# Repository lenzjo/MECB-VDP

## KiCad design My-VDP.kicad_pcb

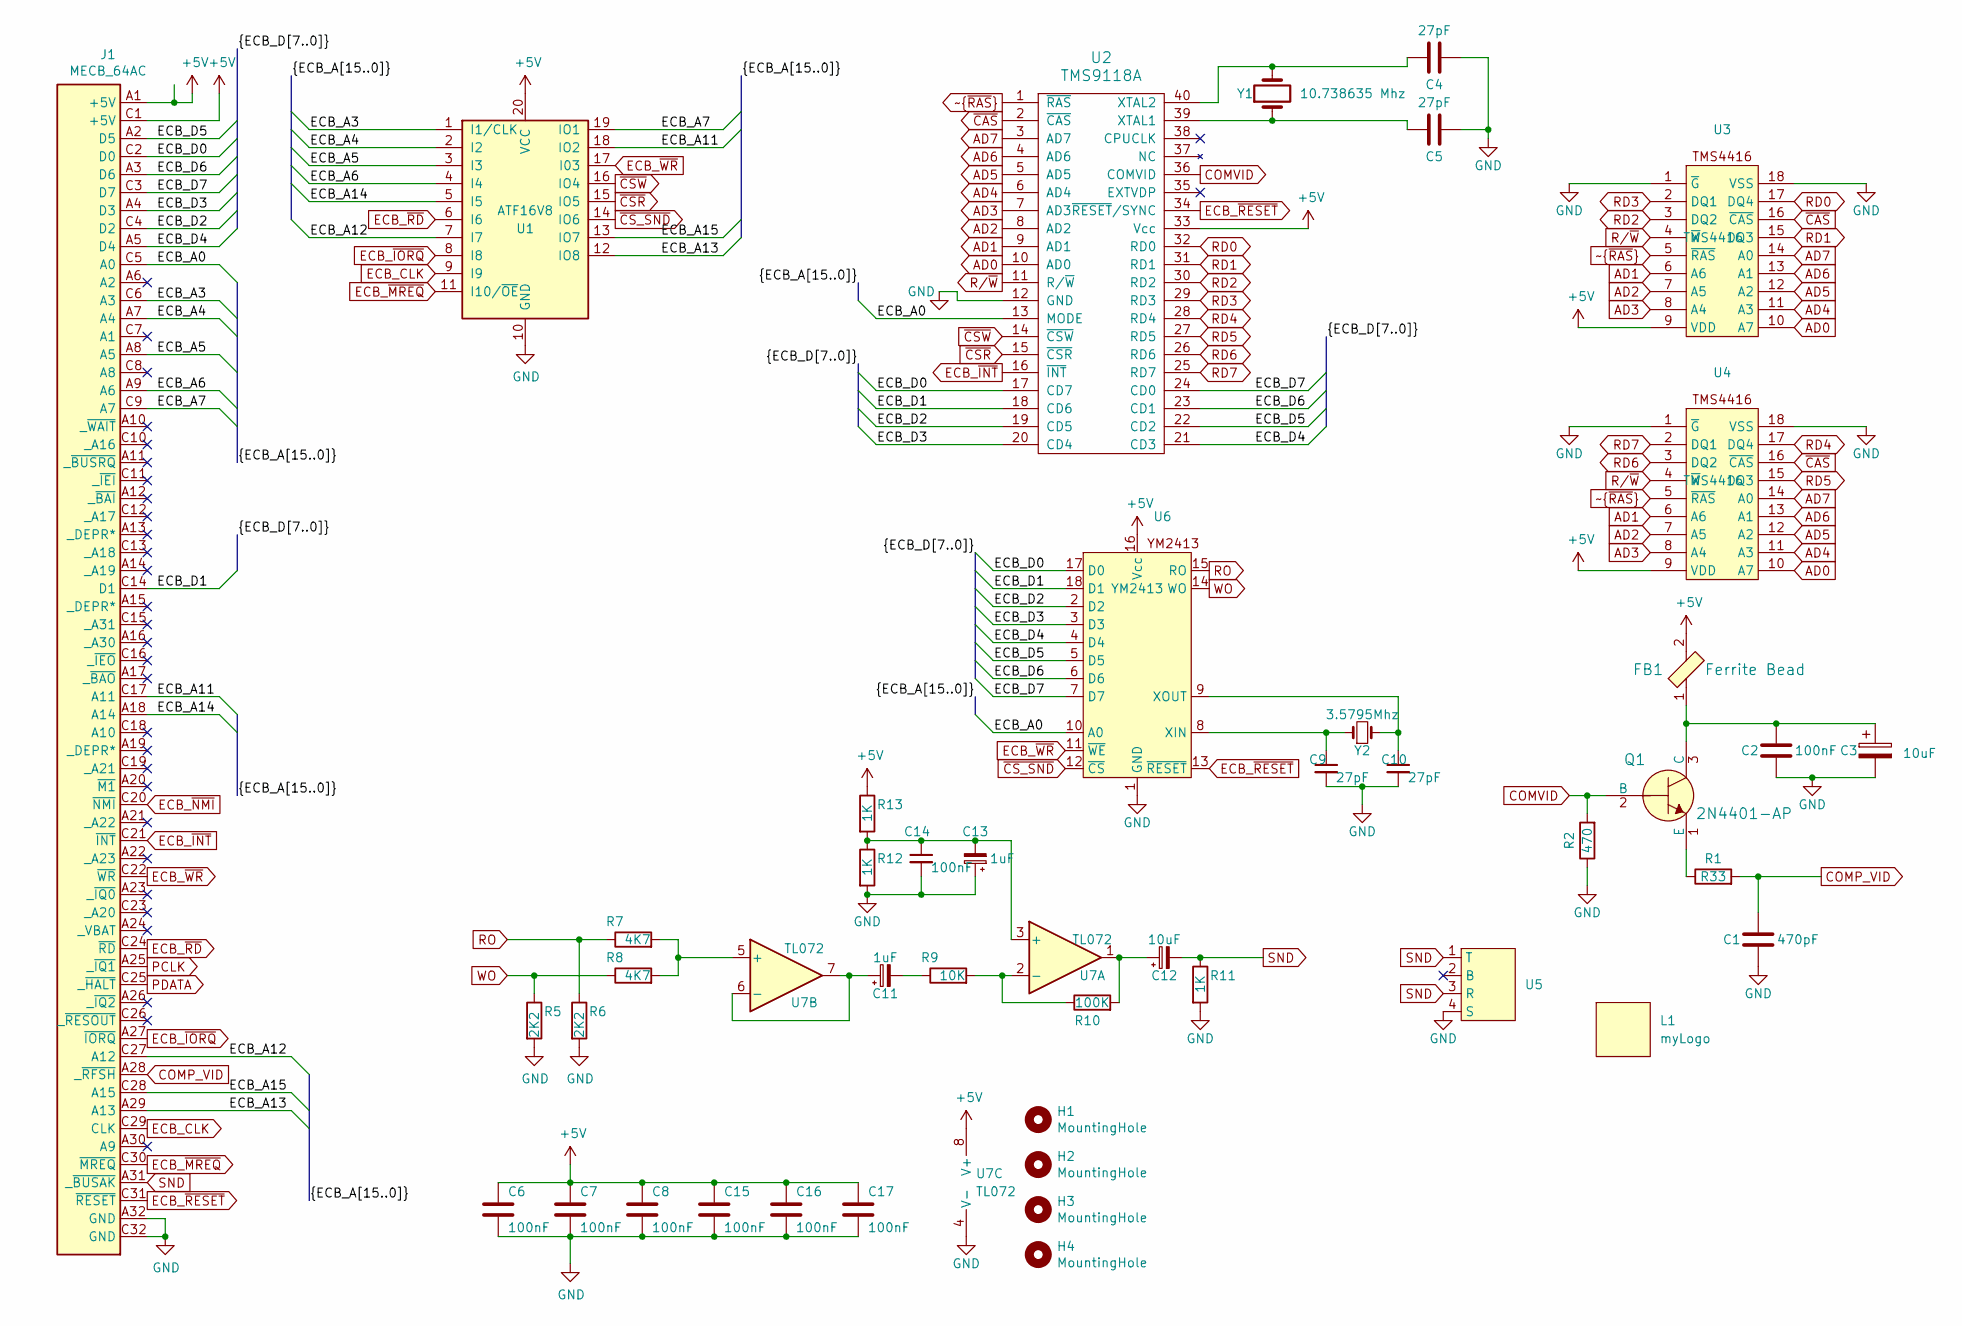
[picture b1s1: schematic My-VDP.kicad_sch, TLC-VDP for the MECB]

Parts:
C1: 470pF; C_Disc_D6.0mm_W2.5mm_P5.00mm
C2, C6, C7, C8, C14, C15, C16, C17: 100nF; C_Disc_D4.7mm_W2.5mm_P5.00mm
C3, C12: 10uF; CP_Radial_D5.0mm_P2.00mm
C4, C5, C9, C10: 27pF; C_Disc_D4.3mm_W1.9mm_P5.00mm
C11, C13: 1uF; CP_Radial_D4.0mm_P2.00mm
FB1: Ferrite Bead; R_Axial_DIN0207_L6.3mm_D2.5mm_P10.16mm_Horizontal; MPN BLM18AG601SN1D; Digi-Key_PN 490-1014-1-ND
H1, H2, H3, H4: MountingHole; MountingHole_3.2mm_M3
J1: MECB_64AC; DIN41612_C_2x32_C64AC_Male_Horizontal_THT
L1: myLogo; LOGO_sm
Q1: 2N4401-AP; TO-92-3_Formed_Leads; MPN 2N4401-AP; Digi-Key_PN 2N4401-APCT-ND
R1: R33; R_Axial_DIN0207_L6.3mm_D2.5mm_P10.16mm_Horizontal
R2: 470; R_Axial_DIN0207_L6.3mm_D2.5mm_P10.16mm_Horizontal
R5, R6: 2K2; R_Axial_DIN0207_L6.3mm_D2.5mm_P10.16mm_Horizontal
R7, R8: 4K7; R_Axial_DIN0207_L6.3mm_D2.5mm_P10.16mm_Horizontal
R9: 10K; R_Axial_DIN0207_L6.3mm_D2.5mm_P10.16mm_Horizontal
R10: 100K; R_Axial_DIN0207_L6.3mm_D2.5mm_P10.16mm_Horizontal
R11, R12, R13: 1K; R_Axial_DIN0207_L6.3mm_D2.5mm_P10.16mm_Horizontal
U1: ATF16V8; DIP-20_W7.62mm_LongPads
U2: TMS9118A; DIP-40_W15.24mm_LongPads
U3, U4: TMS4416; DIP-18_W7.62mm_LongPads
U5: C 6560 s.Audio Socket
U6: YM2413; DIP-18_W7.62mm
U7: TL072; DIP-8_W7.62mm_LongPads
Y1: 10.738635 Mhz; Crystal_HC49-U_Horizontal
Y2: 3.5795Mhz; Crystal_HC49-U_Horizontal

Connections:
+5V: C6.1, C7.1, C8.1, C15.1, C16.1, C17.1, FB1.2, J1.A1 (+5V), J1.C1 (+5V), R13.1, U1.20 (VCC), U2.33 (Vcc), U3.9 (VDD), U4.9 (VDD), U6.16 (Vcc), U7.8 (V+)
/ECB_A0: J1.C5 (A0), U2.13 (MODE), U6.10 (A0)
/ECB_A3: J1.C6 (A3), U1.1 (I1/CLK)
/ECB_A4: J1.A7 (A4), U1.2 (I2)
/ECB_A5: J1.A8 (A5), U1.3 (I3)
/ECB_A6: J1.A9 (A6), U1.4 (I4)
/ECB_A7: J1.C9 (A7), U1.19 (IO1)
/ECB_A11: J1.C17 (A11), U1.18 (IO2)
/ECB_A12: J1.C27 (A12), U1.7 (I7)
/ECB_A13: J1.A29 (A13), U1.12 (IO8)
/ECB_A14: J1.A18 (A14), U1.5 (I5)
/ECB_A15: J1.C28 (A15), U1.13 (IO7)
/ECB_D0: J1.C2 (D0), U2.17 (CD7), U6.17 (D0)
/ECB_D1: J1.C14 (D1), U2.18 (CD6), U6.18 (D1)
/ECB_D2: J1.C4 (D2), U2.19 (CD5), U6.2 (D2)
/ECB_D3: J1.A4 (D3), U2.20 (CD4), U6.3 (D3)
/ECB_D4: J1.A5 (D4), U2.21 (CD3), U6.4 (D4)
/ECB_D5: J1.A2 (D5), U2.22 (CD2), U6.5 (D5)
/ECB_D6: J1.A3 (D6), U2.23 (CD1), U6.6 (D6)
/ECB_D7: J1.C3 (D7), U2.24 (CD0), U6.7 (D7)
AD0: U2.10 (AD0), U3.10 (A7), U4.10 (A7)
AD1: U2.9 (AD1), U3.6 (A6), U4.6 (A6)
AD2: U2.8 (AD2), U3.7 (A5), U4.7 (A5)
AD3: U2.7 (AD3), U3.8 (A4), U4.8 (A4)
AD4: U2.6 (AD4), U3.11 (A3), U4.11 (A3)
AD5: U2.5 (AD5), U3.12 (A2), U4.12 (A2)
AD6: U2.4 (AD6), U3.13 (A1), U4.13 (A1)
AD7: U2.3 (AD7), U3.14 (A0), U4.14 (A0)
COMP_VID: C1.1, J1.A28 (_~RFSH), R1.2
COMVID: Q1.2 (B), R2.2, U2.36 (COMVID)
ECB_CLK: J1.C29 (CLK), U1.9 (I9)
ECB_~INT: J1.C21 (~INT), U2.16 (~INT)
ECB_~IORQ: J1.A27 (~IORQ), U1.8 (I8)
ECB_~MREQ: J1.C30 (~MREQ), U1.11 (I10/~OE)
ECB_~NMI: J1.C20 (~NMI)
ECB_~RD: J1.C24 (~RD), U1.6 (I6)
ECB_~RESET: J1.C31 (~RESET), U2.34 (~RESET/SYNC), U6.13 (~RESET)
ECB_~WR: J1.C22 (~WR), U1.17 (I03), U6.11 (~WE)
GND: C1.2, C2.2, C3.2, C4.2, C5.2, C6.2, C7.2, C8.2, C9.2, C10.2, C13.1, C14.2, C15.2, C16.2, C17.2, J1.A32 (GND), J1.C32 (GND), R2.1, R5.2, R6.2, R11.2, R12.2, U1.10 (GND), U2.12 (GND), U3.1 (~G), U3.18 (VSS), U4.1 (~G), U4.18 (VSS), U5.4 (S), U6.1 (GND), U7.4 (V-)
unnamed: C11.2, R9.1
unnamed: C12.1, R10.2, U7.1
unnamed: C2.1, C3.1, FB1.1, Q1.3 (C)
unnamed: Q1.1 (E), R1.1
unnamed: C5.1, U2.39 (XTAL1), Y1.1
unnamed: C4.1, U2.40 (XTAL2), Y1.2
unnamed: C9.1, U6.8 (XIN), Y2.1
unnamed: C10.1, U6.9 (XOUT), Y2.2
unnamed: C13.2, C14.1, R12.1, R13.2, U7.3 (+)
unnamed: R9.2, R10.1, U7.2 (-)
unnamed: R7.2, R8.2, U7.5 (+)
unnamed: C11.1, U7.6 (-), U7.7
PCLK: J1.A25 (_~IQ1)
PDATA: J1.C25 (_~HALT)
RD0: U2.32 (RD0), U3.17 (DQ4)
RD1: U2.31 (RD1), U3.15 (DQ3)
RD2: U2.30 (RD2), U3.3 (DQ2)
RD3: U2.29 (RD3), U3.2 (DQ1)
RD4: U2.28 (RD4), U4.17 (DQ4)
RD5: U2.27 (RD5), U4.15 (DQ3)
RD6: U2.26 (RD6), U4.3 (DQ2)
RD7: U2.25 (RD7), U4.2 (DQ1)
RO: R6.1, R7.1, U6.15 (RO)
R/~W: U2.11 (R/~W), U3.4 (~W), U4.4 (~W)
SND: C12.2, J1.A31 (_~BUSAK), R11.1, U5.1 (T), U5.3 (R)
WO: R5.1, R8.1, U6.14 (WO)
~CAS: U2.2 (~CAS), U3.16 (~CAS), U4.16 (~CAS)
~CSR: U1.15 (IO5), U2.15 (~CSR)
~CSW: U1.16 (IO4), U2.14 (~CSW)
~CS_SND: U1.14 (IO6), U6.12 (~CS)
~~{RAS}: U2.1 (~RAS), U3.5 (~RAS), U4.5 (~RAS)

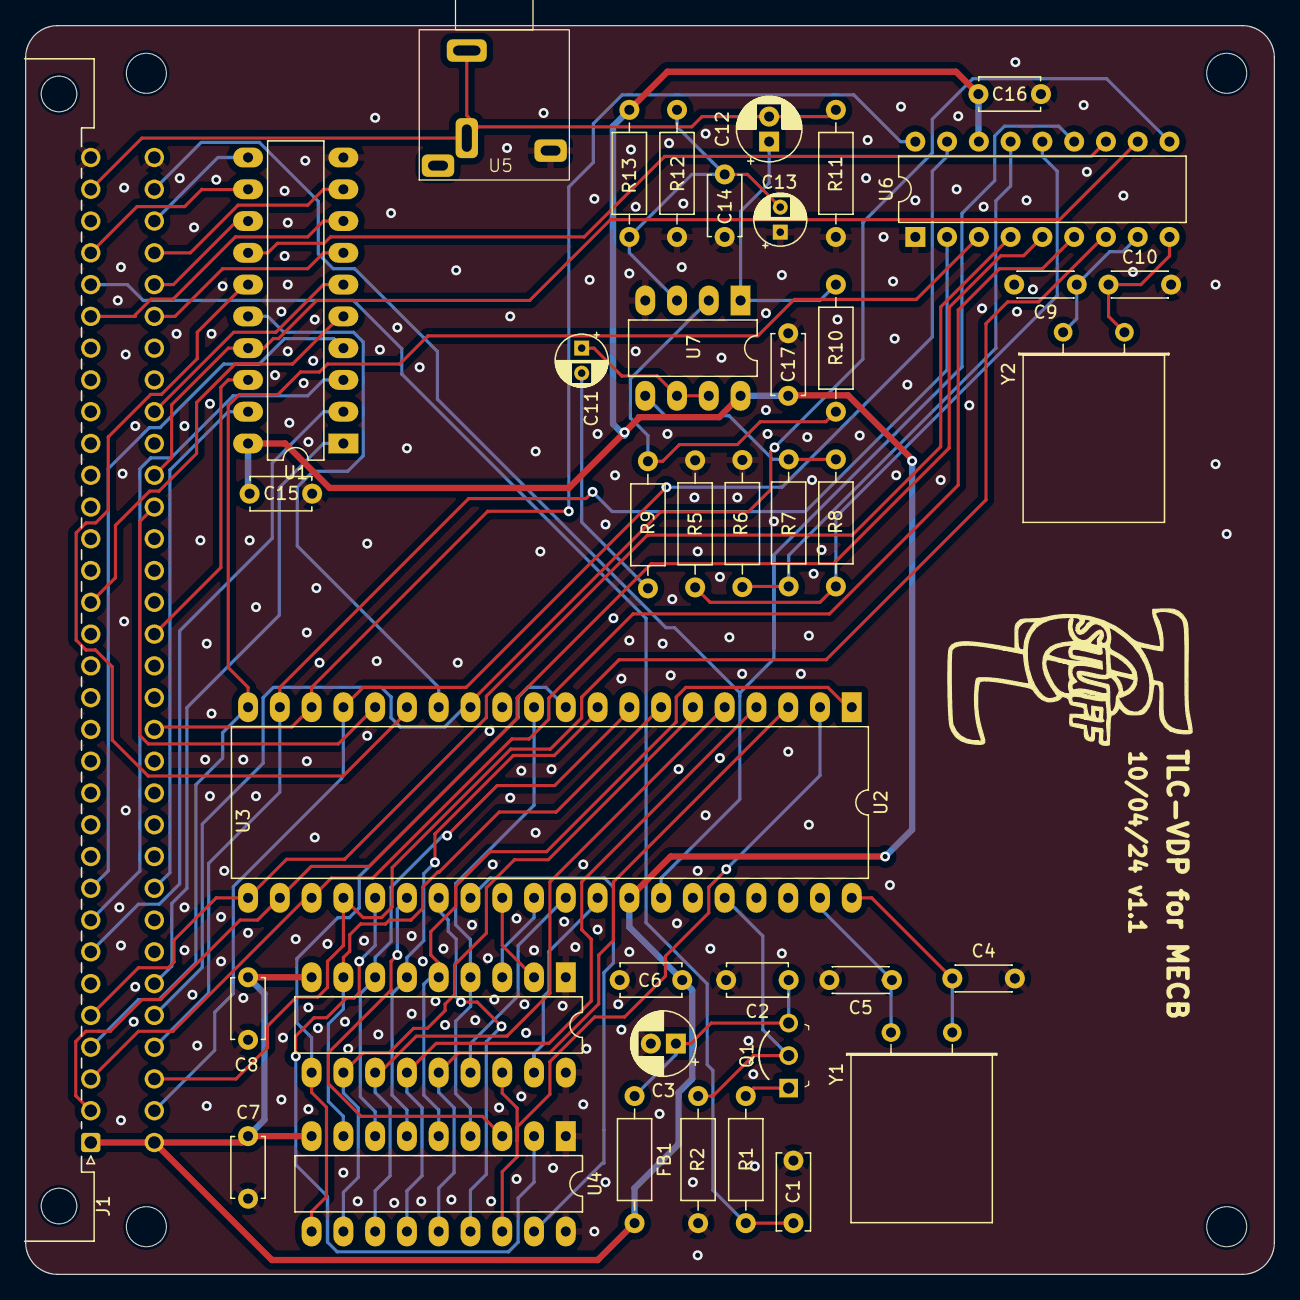
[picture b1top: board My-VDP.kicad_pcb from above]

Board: 2 copper layers, 99.8 x 99.8 mm, 45 parts (0 on the bottom side), 67 nets.
